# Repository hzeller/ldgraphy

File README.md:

LDgraphy - Laser Direct Lithography
===================================

http://ldgraphy.org/

A process also known as Laser Direct Imaging.

[![First Test][run-vid]](https://youtu.be/G9-JK2Nc7w0)

Simple implementation of photo resist exposure using a 405nm laser.
Goal is to have this Open Source/Open Hardware system easy to reproduce with
commonly available parts. The BOM is in the order of $100 including the
Beaglebone Green.

  * 500mW 405nm laser ($30ish)
  * Commonly available polygon mirror scanner (from laser printers) ($20ish)
  * Beaglebone Black/Green to control it all (using the PRU to generate precise
    timings for motors and laser) ($40ish)
  * Stepper motor for linear axis (plus end-stop switches) (scrap box)
  * Photo diode to determine start-of-line (as the polygon mirrors have
    slightly different long faces and also phase-drift over time) (SFH203P)
  * Local electronics: fast Laser diode driver and stepmotor driver (few $$)

Stay tuned for a putting-it-together video once the design is settled.

Here is some [rough design outline][design] in case you are interested in more
details.

Work in Progress
----------------
Currently, the design is [work in progress][LDGraphy-posts] while testing
various different types of commonly available polygon mirrors and lasers. The
[PCBs](./pcb) for the [cape] and the [laser current driver] are in their
first iteration with more focus on easy measurements and removable parts
(e.g. stepper driver and DC/DC converter are external modules) than compact
design. This part of the hardware is likely to change in the
short term; it turns out, for instance, that some polygon mirrors have not
perfectly perpendicular faces. So an additional sensor is needed to correct
for that.

And of course, the software would need a little more bells and whistles
(e.g. a web-server to easily upload Gerber designs).

Having said that, the device is fully operational with a reliable
resolution of ~0.15mm/6mil, which is right up there with basic fab-house
offerings (goal: reliable 0.1mm (4mil) traces and clearance).

[![Resolution test][resolution-thumb]][resolution]

Compile
-------
This compiles on a BeagleBone Green/Black; it requires the PRU on these
computers for hard realtime-switching of the Laser.

```
git clone --recursive https://github.com/hzeller/ldgraphy.git
```

Install relevant packages. We are reading png-images as input, so we need the
library that helps us with that (probably already installed on your system):
```
sudo apt-get update
sudo apt-get install libpng-dev -y
```

Then compile:
```
cd ldgraphy/src
make
```

To properly prepare the GPIOs and the PRU to be used, you have to install
the device tree overlay on your Beaglebone:
```
cd ldgraphy/device-tree
sudo ./start-devicetree-overlay.sh LDGraphy.dts
```

The input is a PNG image. For converting Gerber files to PNG, see the
`gerber2png` tool in the [scripts/](./scripts) directory.

Usage:
```
Usage:
./ldgraphy [options] <png-image-file>
Options:
        -d <val>   : Override DPI of input image. Default -1
        -i         : Inverse image: black becomes laser on
        -x<val>    : Exposure factor. Default 1.
        -o<val>    : Offset in sled direction in mm
        -R         : Quarter image turn left; can be given multiple times.
        -h         : This help
Mostly for testing or calibration:
        -S         : Skip sled loading; assume board already loaded.
        -E         : Skip eject at end.
        -F         : Run a focus round until Ctrl-C
        -M         : Testing: Inhibit sled move.
        -n         : Dryrun. Do not do any scanning; laser off.
        -j<exp>    : Mirror jitter test with given exposure repeat
        -D<line-width:start,step> : Laser Dot Diameter test chart. Creates a test-strip 10cm x 2cm with 10 samples.
```

Case
----
The current version is made out of [laser-cut acrylic](./hardware)
parts to have it easily and cheaply build for everyone who has
access to a laser cutter (hint: your local Hackerspace might have one).

Here, all electronics is mounted on the top for easier measurements and
such. The final version will fit everything inside.

[![Case][case-pic]](./hardware)

Above is current status of the case, which went through some refinements (here
an [earlier case](./img/intermediate-case.jpg) which better shows
the internal arrangement).

This was the first experiment
-------------------------------

#### First Light

|   Setup                | Result
|------------------------|---------------------------------
|    | 

The first test-device was put together with extruded aluminum.
Somewhat crappy first result, but had potential. Exposure time for this 30 mm
long patch was around 90 seconds (for reference: on the right is how the
geometry _should_ look like).

As you can see, the early stages had some issues, e.g. you can't trust the "PLL"
of the mirror to properly lock - it has a phase drift over
time (hence the warped square). The current design has a HSync line sensor.
Overall the [progress] after that improved various
issues seen up to the point where it starts to be usable for PCB work.

[progress]: https://plus.google.com/u/0/+HennerZeller/posts/FeqdPoEZ3AT
[Laser current driver]: ./pcb/laser-drive
[Cape]: ./pcb/cape
[LDGraphy-posts]: https://plus.google.com/u/0/s/%23ldgraphy/top
[run-vid]: ./img/ldgraphy-yt.jpg
[resolution-thumb]: ./img/line-resolution-small.jpg
[resolution]: https://plus.google.com/u/0/+HennerZeller/posts/a8taHWeL5CC
[design]: ./design.md
[case-pic]: ./img/sample-case.jpg

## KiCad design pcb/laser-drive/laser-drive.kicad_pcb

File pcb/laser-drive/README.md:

Laser Driver Board
===================

Laser driver board, a fast current source switchable with a TTL input. Place
this as close as possible to the Laser with short wires.

Choose `R1`, `R5` and `R7` to achieve desired target current for given laser
(`I ≈ (Vref - 0.6) / (R5+R7)`; Vref=0V..5.6V).

Adjust desired current by reference voltage with trimmer before connecting
laser. Measure current through laser via `(+12V - TP4) / R1`.

Depending on the inductivity of the supply line or desired current, not all
of the 10μ caps (C2..C8) might be needed.

### BOM

Qty | Reference(s)              |  Value    |   Footprint
----|---------------------------|-----------|-----------------------------
2   | C1, C11                   | 100n      | 0603
7   | C2, C3, C4, C5, C6, C7, C8| 10u       | 1210
1   | C9                        | 100n      | 0805
1   | C10                       | 100p      | 0603
1   | D1                        | 5V6 zener | SOD-323
1   | J1                        | CONN_01X03| JST_EH_B3B-EH-A_1x03_P2.50mm
1   | P1                        | LaserOut  | JST_EH_B2B-EH-A_1x02_P2.50mm
1   | Q1                        | BCP5616Q  | SOT-223-3
1   | Q2                        | DMN2058UW | SOT-323_SC-70
3   | R1, R5, R7                | 6R2       | 2512
1   | R2                        | 2k2       | 0603
1   | R3                        | 470       | 0603
1   | R6                        | 680       | 0603
1   | R8                        | 1k        | 0603
1   | RV1                       | 10k       | Multi-turn trimmer (through-hole, 2.54mm pitch)
1   | U2                        |  MIC920   | SOT-353_SC-70-5

There are probably better ways to have a fast current switching driver for
lasers that don't have a feedback line. Suggestions welcome.

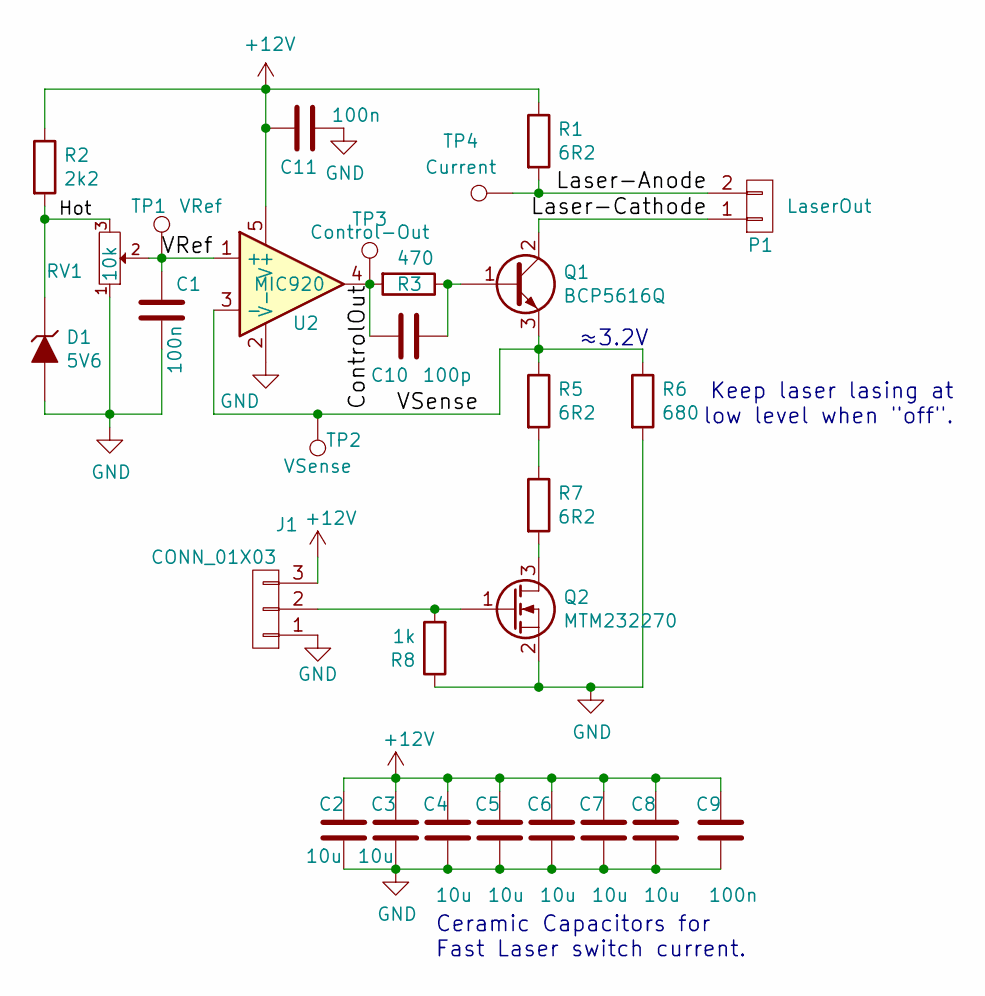
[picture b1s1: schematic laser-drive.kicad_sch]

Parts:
C1, C11: 100n; C_0603_1608Metric
C2, C3, C4, C5, C6, C7, C8: 10u; C_1210_3225Metric
C9: 100n; C_0805_2012Metric
C10: 100p; C_0603_1608Metric
D1: 5V6; D_SOD-323_HandSoldering
J1: CONN_01X03; JST_EH_B3B-EH-A_1x03_P2.50mm_Vertical
P1: LaserOut; JST_EH_B2B-EH-A_1x02_P2.50mm_Vertical
Q1: BCP5616Q; SOT-223-3_TabPin2
Q2: MTM232270; SOT-323_SC-70
R1, R5, R7: 6R2; R_2512_6332Metric
R2: 2k2; R_0603_1608Metric
R3: 470; R_0603_1608Metric
R6: 680; R_0603_1608Metric
R8: 1k; R_0603_1608Metric
RV1: 10k; Potentiometer_Bourns_3296X_Horizontal
TP1: VRef; TestPoint_Pad_D1.5mm
TP2: VSense; TestPoint_Pad_D1.5mm
TP3: Control-Out; TestPoint_Pad_D1.5mm
TP4: Current; TestPoint_Pad_D1.5mm
U2: MIC920; SOT-353_SC-70-5

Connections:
+12V: C2.1, C3.1, C4.1, C5.1, C6.1, C7.1, C8.1, C9.1, C11.2, J1.3, R1.1, R2.1, U2.5 (V+)
/ControlOut: C10.2, R3.2, TP3.1, U2.4
/Hot: D1.1 (K), R2.2, RV1.3
/Laser-Anode: P1.2, R1.2, TP4.1
/Laser-Cathode: P1.1, Q1.2 (C)
/VRef: C1.1, RV1.2, TP1.1, U2.1 (+)
/VSense: Q1.3 (E), R5.1, R6.1, TP2.1, U2.3 (-)
GND: C1.2, C2.2, C3.2, C4.2, C5.2, C6.2, C7.2, C8.2, C9.2, C11.1, D1.2 (A), J1.1, Q2.2 (S), R6.2, R8.1, RV1.1, U2.2 (V-)
unnamed: J1.2, Q2.1 (G), R8.2
unnamed: C10.1, Q1.1 (B), R3.1
unnamed: Q2.3 (D), R7.2
unnamed: R5.2, R7.1

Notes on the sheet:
≈3.2V
Keep laser lasing at low level when "off".
Ceramic Capacitors for Fast Laser switch current.

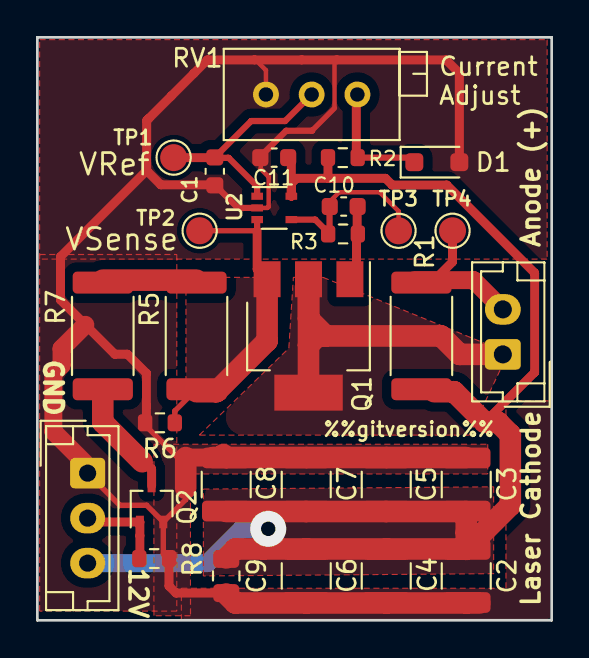
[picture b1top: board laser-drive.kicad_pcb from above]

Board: 2 copper layers, 28.6 x 32.4 mm, 29 parts (0 on the bottom side), 12 nets.

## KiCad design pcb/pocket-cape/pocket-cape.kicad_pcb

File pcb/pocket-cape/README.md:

PocketBeagle LDGraphy cape
==========================

A cape for the PocketBeagle, that will allow to expose double-sided boards.

*Work in progress; won't yet work with the current software and case.*

Not only the software is not adapted yet, but this assume as motor
the 28BYJ-48, yet the acrylic case is still using the larger stepper.

So if you want to build something now, I suggest to use
the [experimental cape](../cape).

The board is packed with connectors; all of which are choosen in a way
that it very hard to connect to the wrong one:

| Designator | Type          | Description
|-----------:|:--------------|:---------------------
| J2         | 2p JST-XH     | Supply voltage. 12-16V
| J5, J8     | 3p JST-PH     | Laser1, Laser2 output
| J1, J3     | 2p JST-PH     | Laser1, Laser2 sync input
| J6, J7     | 5p 0.1" header| Polygon1, Polygon2 mirror
| J4         | 5p JST-XH     | Sled stepper 28BYJ-48
| J10        | 8p FFC 0.5mm  | Connector for 320x200 SPI display
| J9         | 4p JST-PH     | User-interface buttons
| J11        | USB           | USB connector for Wifi dongle

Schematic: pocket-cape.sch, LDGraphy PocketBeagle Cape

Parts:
C1: C; C_0603_1608Metric
C2: 10u; C_1206_3216Metric
C3, C4: 22u; C_1206_3216Metric
C5, C6: 100n; C_0603_1608Metric
D1: MBR230LSFT1G; D_SOD-123
J1: Sync1; JST_PH_B2B-PH-K_1x02_P2.00mm_Vertical
J2: 12..16V; JST_XH_B2B-XH-A_1x02_P2.50mm_Vertical
J3: Sync2; JST_PH_B2B-PH-K_1x02_P2.00mm_Vertical
J4: Sled; JST_XH_B5B-XH-A_1x05_P2.50mm_Vertical
J5: Laser1; JST_PH_B3B-PH-K_1x03_P2.00mm_Vertical
J6: PM1; PinHeader_1x05_P2.54mm_Vertical
J7: PM2; PinHeader_1x05_P2.54mm_Vertical
J8: Laser2; JST_PH_B3B-PH-K_1x03_P2.00mm_Vertical
J9: Switches; JST_PH_B4B-PH-K_1x04_P2.00mm_Vertical
J10: Display; FlatFlexConn-08; PartNo SFv8R-4STBE1HLF
J11: USB1; USB-A-Vertical
L1: 4u7; L_Taiyo-Yuden_NR-60xx
P1, P2: TH-2X18-(35MIL-DIA)-W_O-SILK
R5, R10: 100k; R_0603_1608Metric
R6: 6k2; R_0603_1608Metric
R7: 1k2; R_0603_1608Metric
U1: 74LVC2G14GV; SOT-23-6
U3: ULN2003A; SOIC-16_3.9x9.9mm_P1.27mm
U4: AP3211; SOT-23-6

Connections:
+12V: C2.1, J2.2, J5.3, J6.5, J7.5, J8.3, U4.4 (EN), U4.5 (IN)
/(U1.A1)PWM0A: P1.36
/(U1.A3)PRU-0.4: P1.31
/(U1.A8)AIN0~1.8V: P1.19
/(U1.A10)I2C2.SCL: P1.28
/(U1.A11)I2C1.SDA: P2.11
/(U1.A12)UART0.RX: P1.32
/(U1.A13)SPI0.CLK: P1.8
/(U1.A14)SPI0.CS: P1.6
/(U1.B2)PRU-0.2: P2.32
/(U1.B3)PRU-0.5: P2.34
/(U1.B4)PRU-0.16: P1.20
/(U1.B6)AIN2~1.8V: P1.23
/(U1.B7)VREF+: P1.18
/(U1.B8)AIN1~1.8V: P1.21
/(U1.B9)VREF-: P1.17
/(U1.B10)I2C2.SDA: P1.26
/(U1.B11)I2C1.SCL: P2.9
/(U1.B12)UART0.TX: P1.30
/(U1.B13)SPI0.MISO: P1.10
/(U1.B14)SPI0.MOSI: P1.12
/(U1.C6)AIN3~1.8V: P1.25
/(U1.C7)AIN4~1.8V: P1.27
/(U1.C12)SPI1.MISO: P2.27
/(U1.E1): P1.4
/(U1.F1): P1.35
/(U1.F2)AIN6~3.3V: P1.2
/(U1.L15)USB1.D+: J11.3, P1.11
/(U1.L16)USB1.D-: J11.2, P1.9
/(U1.M14)USB1.DRVVBUS: P1.3
/(U1.N13)AIN7~1.8V: P2.36
/(U1.P5)GPIO-0.23: P2.3
/(U1.P12)PWM1A: P2.1
/(U1.P15)UART4.RX: P2.5
/(U1.R5)GPIO-0.26: P1.34
/(U1.R11)RESET#: P2.26
/(U1.R16)UART4.TX: P2.7
/(U1.T11)PWR.BTN: P2.12
/(U1.T16): P2.2
/BAT.TEMP: P2.16
/FB: R6.2, R7.1, U4.3 (FB)
/SW: C1.2, D1.1 (K), L1.1, U4.6 (SW)
BUTT_1: J9.2, P2.17
BUTT_2: J9.3, P2.19
BUTT_3: J9.4, P2.20
DISP-CLK: J10.3, P2.29
DISP-CS: J10.4, P2.31
DISP-DC: J10.5, P2.33
DISP-MOSI: J10.2, P2.25
DISP-RST: J10.6, P2.35
GND: C2.2, C3.2, C4.2, C5.1, C6.1, D1.2 (A), J1.1, J2.1, J3.1, J5.1, J6.4, J7.4, J8.1, J9.1, J10.7, J10.9, J11.4, J11.5, P1.13, P1.15, P1.16, P1.22, P2.15, P2.21, R7.2, U1.2 (GND), U3.3 (I3), U3.5 (I5), U3.6 (I6), U3.8 (GND), U3.11 (O6), U3.12 (O5), U3.14 (O3), U4.2 (GND)
LASER1: J5.2, P1.29
LASER2: J8.2, P1.33
MIRROR_CLK: J6.1, J7.1, P2.10
unnamed: C1.1, U4.1 (BS)
unnamed: J1.2, R5.1, U1.1
unnamed: J3.2, R10.1, U1.3
unnamed: J4.1, U3.10 (O7)
unnamed: J4.2, U3.13 (O4)
unnamed: J4.3, U3.15 (O2)
unnamed: J4.4, U3.16 (O1)
STEP_A1: P2.8, U3.7 (I7)
STEP_A2: P2.22, U3.2 (I2)
STEP_B1: P2.18, U3.4 (I4)
STEP_B2: P2.24, U3.1 (I1)
SYS_5V: P2.13
SYS_VOUT: J11.1, P1.5, P1.24
Sync1: P2.28, U1.6
Sync2: P2.30, U1.4
VDD_3V3B: C5.2, J10.1, P2.23, U1.5 (VCC)
VDD_5V: C3.1, C4.1, C6.2, J4.5, L1.2, P1.1, R5.2, R6.1, R10.2, U3.9 (COM)
VIN.BAT: P2.14
~MIRROR_EN1: J6.3, P2.4
~MIRROR_EN2: J7.3, P2.6

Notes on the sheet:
NC on 8 to make accidentally turned cable less dangerous. (pin 9 = connector shield)

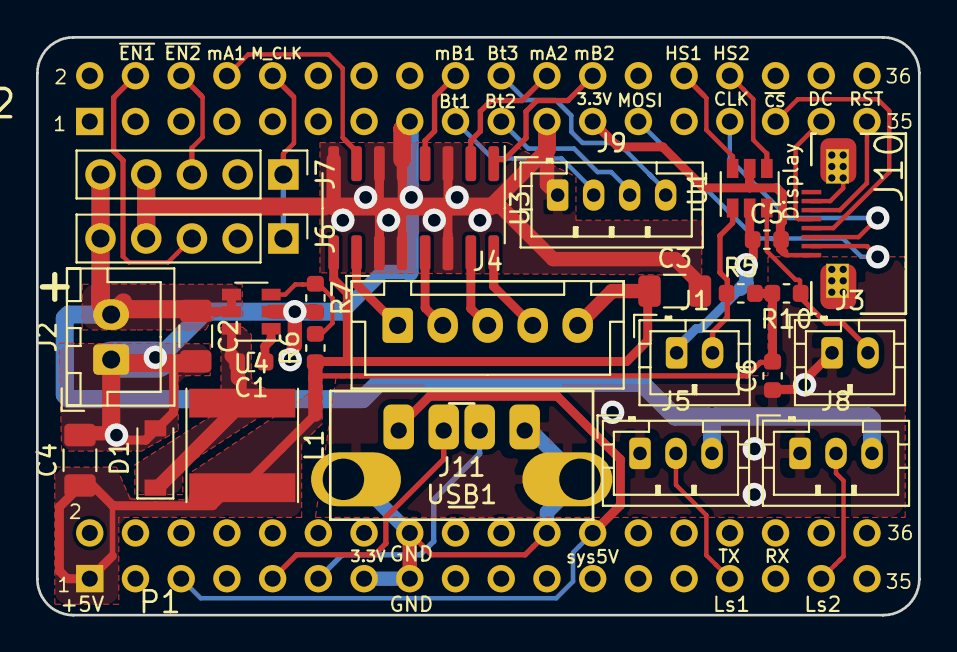
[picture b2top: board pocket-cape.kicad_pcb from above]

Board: 2 copper layers, 49.0 x 32.1 mm, 28 parts (0 on the bottom side), 35 nets.

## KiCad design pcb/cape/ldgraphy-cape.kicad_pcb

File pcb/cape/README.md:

LDGraphy Beaglebone Black cape
==============================

This is for the experimental set-up. This is not meant to
be final, it focuses on easy measurement and mostly being a break-out for
connectors for other parts. The final board will have all the parts that are now
external modules integrated on one board.

  * Single 12V supply (uses a MP1584 based module to generate 5V supply for
    Beaglebone).
  * Inputs
     - Connector for photo diode used for the horizontal sync detection.
       Amplifier and Schmitt Trigger with fast OpAmps ([MIC920] datasheet)
       and steep enough slew-rate to generate acceptable output for digital
       inputs (also, same as used in the [laser driver](../laser-drive) to keep
       BOM small).
     - Two end-switches inputs.
     - One "user interface"-button input.
  * Outputs
     - Laser output connector for external [laser driver](../laser-drive).
     - Polygon mirror pulses and enable via 5-pin Polygon mirror connector.
     - Stepper motor (In this set-up: simply using a Pololu module)

(TODO: update schematic: there is now a cap accross R14)

[MIC920]: http://ww1.microchip.com/downloads/en/DeviceDoc/mic920.pdf

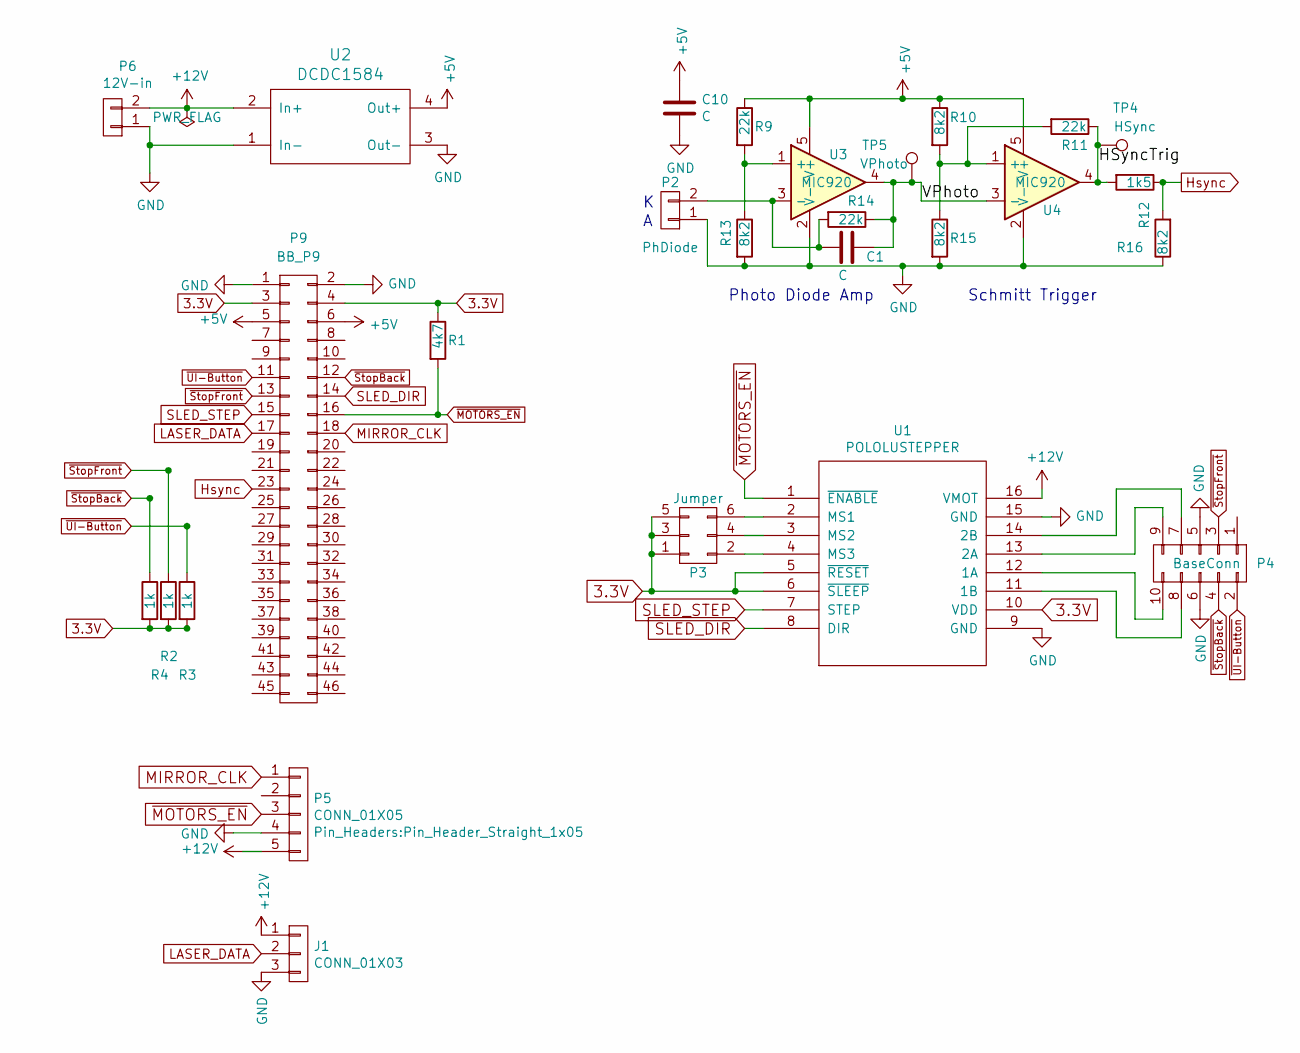
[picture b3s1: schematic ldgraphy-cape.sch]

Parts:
C1, C10: C; C_0603
J1: CONN_01X03; Pin_Header_Straight_1x03_Pitch2.54mm
P2: PhDiode; Pin_Header_Straight_2x01_Pitch2.54mm
P3: Jumper; Pin_Header_Straight_2x03_Pitch2.54mm_SMD
P4: BaseConn; Pin_Header_Straight_2x05_Pitch2.54mm_SMD
P5: CONN_01X05; Pin_Header_Straight_1x05
P6: 12V-in; Pin_Header_Straight_1x02_Pitch2.54mm
P9: BB_P9; Pin_Header_Straight_2x18_Pitch2.54mm
R1: 4k7; R_0603
R2, R3, R4: 1k; R_0603
R9, R11, R14: 22k; R_0603
R10, R13, R15, R16: 8k2; R_0603
R12: 1k5; R_0603
TP4: HSync; Measurement_Point_Round-SMD-Pad_Small
TP5: VPhoto; Measurement_Point_Round-SMD-Pad_Small
U1: POLOLUSTEPPER; POLOLU
U2: DCDC1584; dcdc-mp1584
U3, U4: MIC920; SOT-353_SC-70-5

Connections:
3.3V: P3.1, P3.3, P3.5, P9.3, P9.4, R1.1, R2.2, R3.2, R4.2, U1.5 (~RESET), U1.6 (~SLEEP), U1.10 (VDD)
+5V: C10.1, P9.5, P9.6, R9.1, R10.1, U2.4 (Out+), U3.5 (V+), U4.5 (V+)
+12V: J1.1, P5.5, P6.2, U1.16 (VMOT), U2.2 (In+)
/HSyncTrig: R11.1, R12.2, TP4.1, U4.4
/VPhoto: C1.1, R14.1, TP5.1, U3.4, U4.3 (-)
GND: C10.2, J1.3, P2.1, P4.5, P4.6, P5.4, P6.1, P9.1, P9.2, R13.2, R15.2, R16.1, U1.9 (GND), U1.15 (GND), U2.1 (In-), U2.3 (Out-), U3.2 (V-), U4.2 (V-)
Hsync: P9.23, R12.1, R16.2
LASER_DATA: J1.2, P9.17
MIRROR_CLK: P5.1, P9.18
unnamed: C1.2, P2.2, R14.2, U3.3 (-)
unnamed: P3.2, U1.4 (MS3)
unnamed: P3.4, U1.3 (MS2)
unnamed: P3.6, U1.2 (MS1)
unnamed: P4.7, U1.14 (2B)
unnamed: P4.8, U1.11 (1B)
unnamed: P4.9, U1.13 (2A)
unnamed: P4.10, U1.12 (1A)
unnamed: R10.2, R11.2, R15.1, U4.1 (+)
unnamed: R9.2, R13.1, U3.1 (+)
SLED_DIR: P9.14, U1.8 (DIR)
SLED_STEP: P9.15, U1.7 (STEP)
~MOTORS_EN: P5.3, P9.16, R1.2, U1.1 (~ENABLE)
~StopBack: P4.4, P9.12, R4.1
~StopFront: P4.3, P9.13, R2.1
~UI-Button: P4.2, P9.11, R3.1

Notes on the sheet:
Schmitt Trigger
Photo Diode Amp

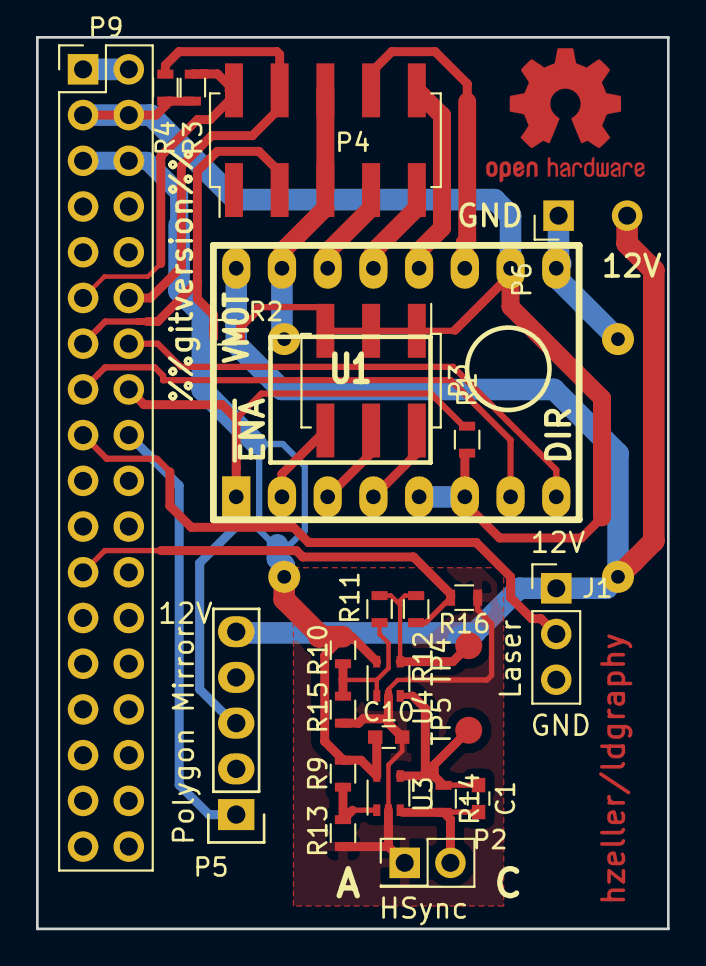
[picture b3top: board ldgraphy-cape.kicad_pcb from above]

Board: 2 copper layers, 35.1 x 49.5 mm, 27 parts (1 on the bottom side), 25 nets.

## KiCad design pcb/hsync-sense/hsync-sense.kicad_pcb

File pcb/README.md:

LDGraphy PCBs
=============

Some boot-strapping required ... we need these PCBs first, before we can make
PCBs :)

  * [Laser driver](./laser-drive): fast current source to drive Lasers. Often,
    the Lasers you can buy come with their own driver, but they are very slow.
    This one is meant to switch >= 1Mhz while behaving as a current source.
  * [Beaglebone cape](./cape): a cape for the
    Beaglebone Black or Green providing all the connections to various
    parts of the set-up. This was the first version mostly for experimenting
    and successfully used.
  * [PocketCape](./pocket-cape): The new cape, ready for the cheaper
    and smaller PocketBeagle.
    Unlike the experimental board that used a DC/DC converter and stepmotor
    driver as separate modules, this has everything on-board.
    It is ready for double-sided boards with two outputs for lasers, polygon
    mirrors and two inputs for horizontal sync detection.

In the current set-up, they are mounted externally to provide easy access for
measuring various aspects. After the dust settles, they will all fit in the
LDGraphy case.

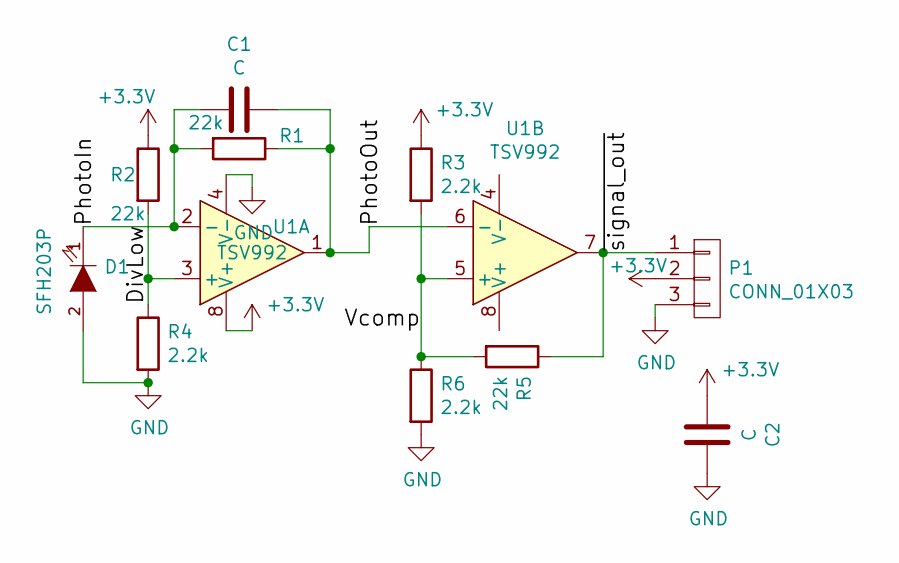
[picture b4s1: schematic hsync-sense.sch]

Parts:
C1, C2: C; C_0603
D1: SFH203P; LED-5MM
P1: CONN_01X03; Pin_Header_Straight_1x03
R1, R2, R5: 22k; R_0603
R3, R4, R6: 2.2k; R_0603
U1: TSV992; MSOP-8-1EP_3x3mm_Pitch0.65mm

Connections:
+3V3: C2.2, P1.2, R2.1, R3.1, U1.8 (V+)
/DivLow: R2.2, R4.1, U1.3 (+)
/PhotoIn: C1.2, D1.1 (K), R1.2, U1.2 (-)
/PhotoOut: C1.1, R1.1, U1.1, U1.6 (-)
/Vcomp: R3.2, R5.2, R6.1, U1.5 (+)
/~signal_out: P1.1, R5.1, U1.7
GND: C2.1, D1.2 (A), P1.3, R4.2, R6.2, U1.4 (V-)

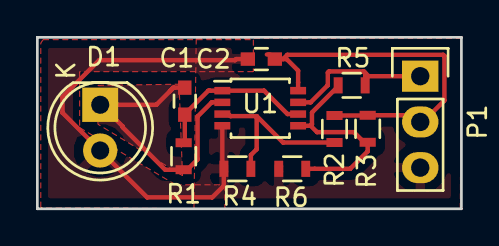
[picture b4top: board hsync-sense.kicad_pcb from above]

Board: 2 copper layers, 23.6 x 9.5 mm, 11 parts (0 on the bottom side), 7 nets.

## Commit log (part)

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2016-12-30 o initial add.
2017-01-01 o Add motor mount.
2017-01-01 o Add side mount.
2017-01-01 o add polygon mirror mount.
2017-01-02 o First Beaglebone PRU boilerplate stuff
2017-01-02 o Add some image.
2017-01-03 o Prepare DTS for more output bits (for the sled stepper motor) o Make PRU code more readable by assigning some variables to fixed registers and name them using the .struct feature.
2017-01-04 o update readme.
2017-01-06 o Move BitArray in container.h header o Move ScanLineSender in its own .h/.cc file.
2017-01-06 o More queing to avoid unnecessary buffer underruns.
2017-01-06 o crude hack to choose sled-stepper to be turning from host. o Add -F focus wait initially o Reduce CPU use
2017-01-09 o add acme screw holder (Thanks to Miloh).
2017-01-22 o Remove first generation laser cut parts.
2017-01-22 o A little test-pattern for exposure experiments.
2017-01-23 o Make mirror mount better fit the actual mirror.
2017-01-24 o Make it easier to choose individual components to cut.
2017-01-25 o remove obsolete print-part
2017-01-29 o change to linear scan.
2017-01-30 o make top and bottom slides separately configurable. o side-panels: screw on towards device.
2017-01-30 o Add bottom part holding stepper and bearing, all mounted on a base-plate for easy assembly and work.
2017-01-31 o Update hardware README with different layers. o Show sample render of cuts.
2017-02-01 o Add finger holes at the bottom to better access side-nuts when case is closed.
2017-02-01 o inner width of drive-train was off: need to substract the slide width.
2017-02-01 o Organize cut parts from bottom up.
2017-02-03 o Take offset into account and manually translate.
2017-02-03 o Add script to convert gerbers.
2017-02-05 o Move cape in separate directory.
2017-02-05 o Some number tweaking o a bit more useful diagnostic output.
2017-02-05 o Sidepanel with higher 'apron' o front/back screwed towards width, not length (otherwise the screws scratch on the siderails)
2017-02-06 o No screws anymore in the top-panel.
2017-02-07 o Round front-corners a bit for more pleasing look.
2017-02-09 o Add relief at inner corners that are meant to press-fit.
2017-02-09 o Update sample case.
2017-02-13 o Read hsync sensor to synchronize.
2017-02-14 o Refine test pattern: new goal of 0.1mm to have a margin for typical needed resolution. o Correct for some over-thickness of lines that ghostscript creates when rendering bitmaps.
2017-02-15 o add hsync diffusor + photo diode.
2017-02-17 o Add a black/white postscript converter that directly generates png. It is faster and can embed the resolution.
2017-02-18 o Use PNG library directly - it is much faster getting the pixels out of it than with ImageMagick
2017-02-18 o Make gerber2png output PNGs with properly set resolution in the meta data. Unfortunately, gerbv can't do that (thanks to deficiencies in Cairo and gerbv, patches on the way), so use gerbv first to 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
2017-02-18 o Make DPI overridable.
2017-02-21 o Provide space for photo diode leads.
2017-02-24 o Add License file.
2017-02-25 o work around issues with stupid old compilers
2017-02-25 o Update image.
2017-03-05 o Add simple way to add measurement lines.
2017-03-05 o slightly nicer arrow appearance.
2017-03-05 o Make slot lines work for horizontal and vertical.
2017-03-05 o Add description title of sub-parts o Add wire-management hole for switch.
2017-03-05 o Description: only show if print-measures is on.
2017-03-05 o Fix drive-train missing fingers.
2017-03-05 o Add alignment holes for pcb frame and sled
2017-03-05 o The drive machanics might force a minimum length.
2017-03-07 o Fix redirect angle (half angle for reflection) o Move /scan-angle closer to the other main modify examples. o Temporary: an experiment to provide multiple angles to play with.
2017-03-11 o Make apron arc down all the way to the top-panel. This will make it simpler to have a living-hing cover. o Prepare connecting a living hinge thing by adding connection slots on the top.
2017-03-14 o Manually do clipping as path-clipping does not make it through to the DXF conversion. o Name it kerf-bend instad of living-hinge as this is what we're using it as permanent bend. o still not tested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
2017-03-15 o Tweaking.
2017-03-17 o Less spacing (not tested yet).
2017-03-18 o Add motor footprint for visual reference.
2017-03-23 o Make filenames easier to digest for OshPark.
2017-03-26 o laser driver: change to use OpAmp.
2017-03-28 o Add pictures for laser driver.
2017-03-28 o Add reference SC70 3D package.
2017-03-31 o Fix issues with overlapping copper planes.
2017-04-01 o Add more clearance around GND between pins of SC70
2017-04-01 o Update PCB renderings.
2017-04-02 o Change footprint trimmer to actual size.
2017-04-06 o Sketch out cape. NB: different GPIO assignment than current software expects.
2017-04-21 o First experiment with a sled spring. Not tested in RL yet.
2017-04-22 o Update laser-cut image.
2017-05-22 o Add BeagleBone mounting holes.
2017-05-26 o Update values in schematics.
2017-05-27 o Set right mode for GPIO pins to input.
2017-05-29 Provide loading feature making it simple to enter and remove board.
    o Simple user-space stepper control for the sled. This is only really
    useful for testing, as the timing is of course jittery in non-realtime.
2017-05-29 Sled control: support dryrun. Exposure: allow factor.
    o The sled control now supports a dryrun option, so that -n works
    with it.
    o Exposure can get a factor for exposure time.
2017-05-29 Add mirror tilt jitter test exposure; provide offset option.
    o The mirrors in some polygon mirrors have slight tilt errors
    resulting in jitter in the sled direction. Add an option that
    creates an exposure line in which each mirror face is responsible
    for one part of the line; the resulting 'steps' between lines is
    the error (preparation for later correcting for that).
    o Add an option to start exposure with an offset in sled direction.
2017-05-31 gerber2png: have all images align.
2017-05-31 Make eject switchable; update README.
2017-05-31 Add a little bit more margin around b/w PostScript->PNG conversions.
2017-06-04 Non-tented via for laser driver for single-sided etching.
2017-06-05 Improve gerber2png script.
    o There are now options for resolution (with a default) and
    making 'large' holes.
    o Test for existence of gerbv binary and lament usefully if
    it is not found.
2017-06-05 Add image rotating function.
2017-06-05 Add -R rotate command line option.
2017-06-05 Document -R rotate option in help output.
2017-06-06 Removal: Don't need old hsync-sense anymore. This is now part of the cape.
2017-06-07 Configure tangens calculation to new hardware with different mirror distance.
2017-06-08 Better naming of focus diameter settings.
2017-06-08 Add continuous line resolution chart to determine cut-off resolution.
2017-06-09 Reset accidentally set debug value.
2017-06-09 No delegating constructors in gcc on the BeagleBone :/
2017-06-09 Actually expose Laser Dot chart.
2017-06-10 Case: don't add unnecessary drill holes for cables (cableing changed).
2017-06-10 Fix bounding box of resolution snake test.
2017-06-10 Free mirror clock from 2^x constraint. Any multiple is possible now.
2017-06-10 Tweak laser dot diameter for current machine.
2017-06-11 ConvertBlackWhite: fix bug; ThinImageStructures: don't overwrite currently read image.
    o ConvertBlackWhite: initialization error of the bitmask variable.
    o ThinImageStructure: make work as before - don't change value of pixel
    while we read from image (worked before because we used multi-levels)
2017-06-12 README update with video thumbnail; some text polishing.
2017-06-12 Add missing line-resolution thumbnail.
2017-06-15 Don't use SimpleImage anymore, directly convert to Bitmap at read.
    o High resolution images can take quite a bit of memory, but we
    ever only deal with a bitmap afterwards. Directly convert the PNG
    to a Bitmap as soon as we read it. Saves memory and one more
    conversion.
    o Make CreateRotatedImaage() take a Bitmap as input. This allows
    to use fast bit operations to do the rotation.
2017-06-15 Adjust bed-width calibration.
2017-06-15 Off-by-one. Oh, how I love thee.
    Not.
2017-06-16 Add a design document.
2017-06-16 Design doc: add an image for the arc projecting experiment.
2017-06-17 Add an illustration of a plain arc scan.
2017-06-17 Show remaining time in minutes.
2017-06-17 Make titles in animations a bit more readable.
2017-06-18 Test image: resolution of scan line.
    o Mirror jitter matters and can make a line get worse over its
    progress. Also focus of course. This test image helps to
    test that.
2017-06-18 Move test patterns from img/ to test-patterns/
2017-06-21 Provide status byte PRU->Host; some optimizations.
    o Have a byte that we can send back from PRU to the Host, such as
    error states. This way we can distinguish various error states.
    o Whenever we run out of time for a state, fail immediately with
    an error state so that this is noticeable and can be optimized.
    o Optimize a little. Read laser via r31 instead of GPIO input which
    seems to be pretty slow.
2017-06-22 Add energy units/area unit to make exposure comparable.
    Unfortunately, we don't know the actual optical output of the
    laser, so right now, this is a guess.
2017-06-25 Acrylic spring: outside cut; add DC jack hole on back.
    o The Acrylic springs used on the sled were just one piece, but
    it is more natural considering them part of an outer frame and
    a cut-out to provide the springiness.
    o Add hole to mount a standard 5.5mm DC jack to power the device
    on the back.
2017-07-08 Make usage() message more useful for dot line pattern.
2017-07-13 Also use aux origin for drill files
2017-08-17 Update am335x package.
2017-09-10 Add photo diode compensating cap in feedback loop.
2017-09-28 Start pocket-beagle cape.
2017-09-29 First rough routing of a PocketBeagle cape.
2017-09-30 Adjust header distance to accomodate space to use JST XH headers.
2017-09-30 Fix wrong connection to stepper connector.
    o common is not the center tap, but Pin5
    o Also some more labelling (e.g. adding RX/TX)
2017-09-30 Use three-way connector for Laser (GND - signal - 12V)
2017-10-05 Intermediate state: initial display and USB connector.
    o Add flat flex connector to drive a simple SPI-based display.
    o Try to cram a vertial USB connector onto the board to be able
    to have a wifi dongle.
2017-10-05 Round corners on pocket-cape.
2017-10-05 Improve silkscreen.
    o Label signals directly on header for easier measurements.
    o Arrange partially obstructed component labels.
2017-10-08 Little tweaks (silk-screen; adding 100nF on 3.3V rail)
2017-10-08 Import all net names to PCB.
2017-10-08 Move P1 reference where it is on the PocketBeagle board for easier matching.
2017-10-08 Don't show unnecessary layers.
2017-10-29 Update values in Schematic; directly connect USB 5V with DC/DC 5V.
2017-10-29 o work in progress.
2017-10-29 Remove some non-needed libraries from the Schematic.
2017-10-29 Label motor phases on GPIO header for easier measurements.
2017-10-30 More via stitching between GND planes.
    Mostly to heatsink ULN2003, but also in other places to reduce
    impedance.
2017-11-02 playing with placement.
2018-02-19 Adapt to pstoedit 3.71
2019-04-21 Slowly converting to current kicad.
2019-04-22 More update: convert to 5.x kicab libraries.
2023-07-21 Add a shell.nix for ease of getting needed dependencies.
2023-07-23 Laser driver: Update to current KiCAD
2023-07-23 Update images.
